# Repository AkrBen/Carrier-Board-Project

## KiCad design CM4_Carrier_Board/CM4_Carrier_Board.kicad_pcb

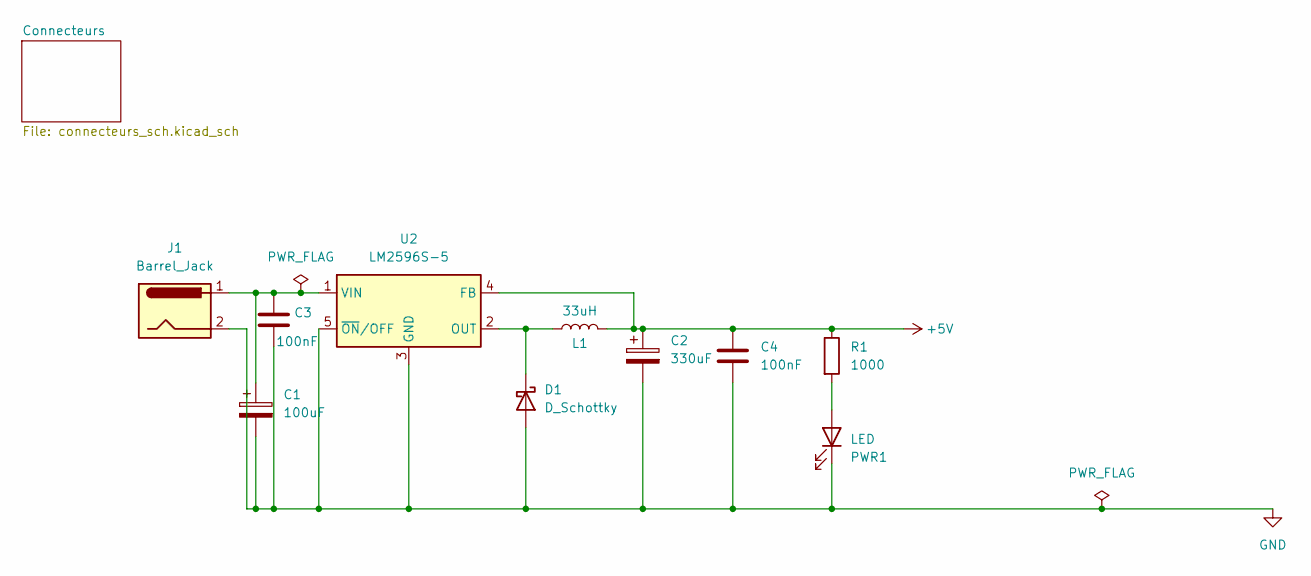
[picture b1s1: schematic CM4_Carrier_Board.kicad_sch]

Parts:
C1: 100uF; CP_Radial_D8.0mm_P3.50mm
C2: 330uF; CP_Radial_D8.0mm_P3.50mm
C3, C4: 100nF; C_Disc_D5.0mm_W2.5mm_P2.50mm
D1: D_Schottky; D_0603_1608Metric
J1: Barrel_Jack; BarrelJack_CUI_PJ-063AH_Horizontal
L1: 33uH; L_0603_1608Metric
PWR1: LED; LED_0603_1608Metric
R1: 1000; R_0603_1608Metric
U2: LM2596S-5; TO-263-5_TabPin3

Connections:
+5V: C2.1, C4.1, L1.2, R1.1, U2.4 (FB); also elsewhere on the board
GND: C1.2, C2.2, C3.2, C4.2, D1.2 (A), J1.2, PWR1.1 (K), U2.3 (GND), U2.5 (~ON/OFF); also elsewhere on the board
unnamed: D1.1 (K), L1.1, U2.2 (OUT)
unnamed: PWR1.2 (A), R1.2
unnamed: C1.1, C3.1, J1.1, U2.1 (VIN)

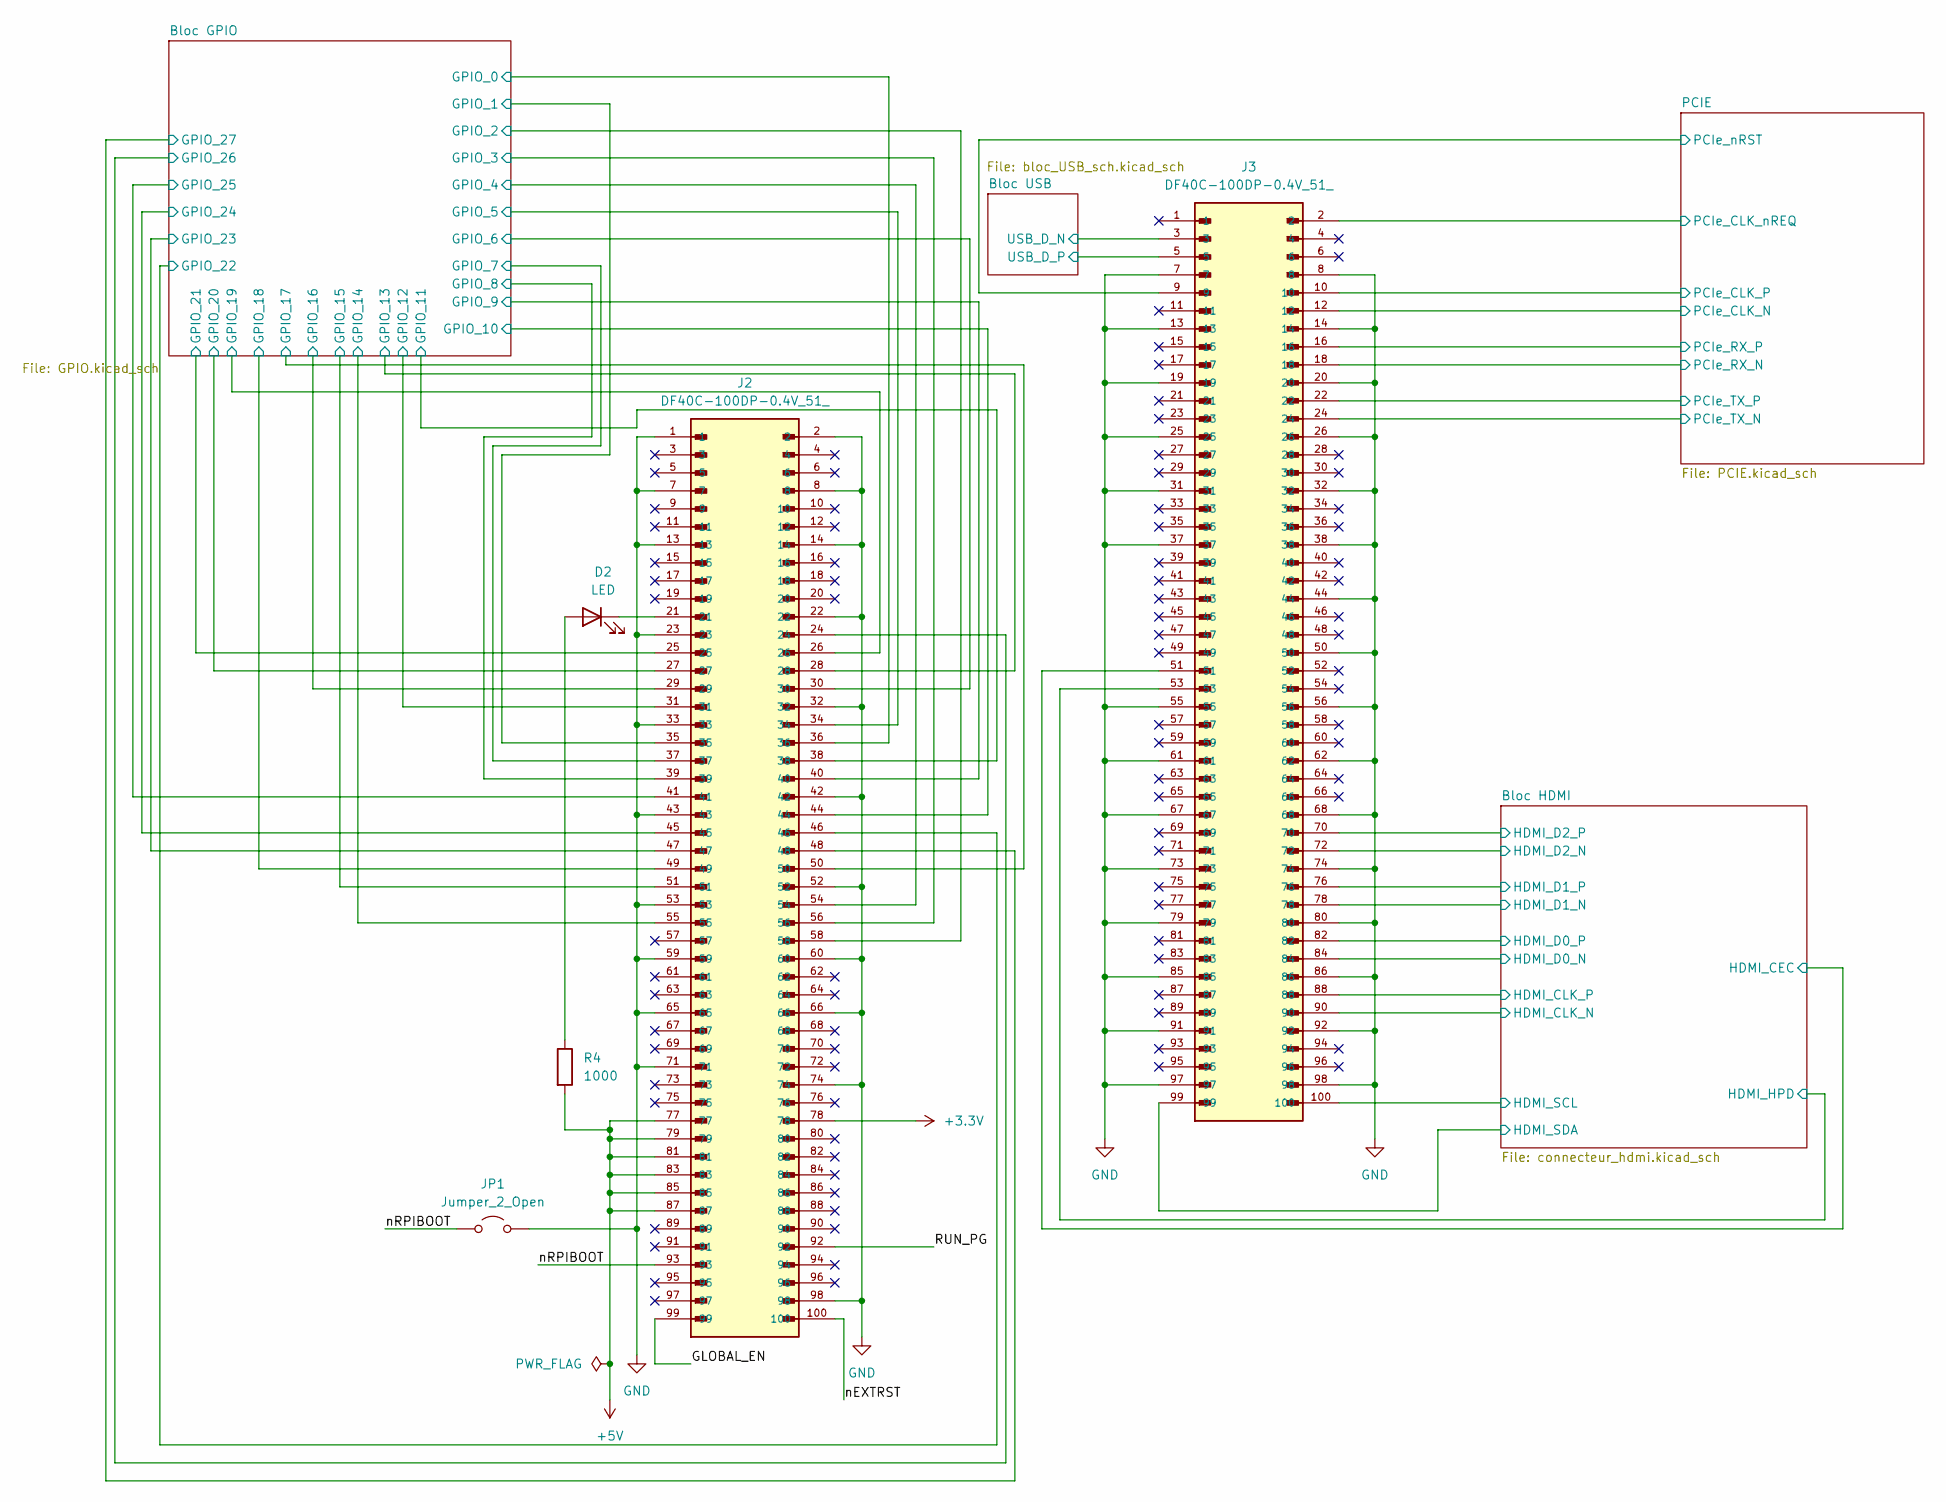
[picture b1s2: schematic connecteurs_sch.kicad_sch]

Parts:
D2: LED; LED_0603_1608Metric
J2, J3: DF40C-100DP-0.4V_51_; HIROSE_DF40C-100DP-0.4V_51_; PARTREV 8
JP1: Jumper_2_Open; PinHeader_1x02_P2.54mm_Vertical
R4: 1000; R_0603_1608Metric

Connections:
+3.3V: J2.78; also elsewhere on the board
+5V: J2.77, J2.79, J2.81, J2.83, J2.85, J2.87, R4.2; also elsewhere on the board
/Connecteurs/Bloc GPIO/GPIO_0: J2.36; also elsewhere on the board
/Connecteurs/Bloc GPIO/GPIO_1: J2.35; also elsewhere on the board
/Connecteurs/Bloc GPIO/GPIO_2: J2.58; also elsewhere on the board
/Connecteurs/Bloc GPIO/GPIO_3: J2.56; also elsewhere on the board
/Connecteurs/Bloc GPIO/GPIO_4: J2.54; also elsewhere on the board
/Connecteurs/Bloc GPIO/GPIO_5: J2.34; also elsewhere on the board
/Connecteurs/Bloc GPIO/GPIO_6: J2.30; also elsewhere on the board
/Connecteurs/Bloc GPIO/GPIO_7: J2.37; also elsewhere on the board
/Connecteurs/Bloc GPIO/GPIO_8: J2.39; also elsewhere on the board
/Connecteurs/Bloc GPIO/GPIO_9: J2.40; also elsewhere on the board
/Connecteurs/Bloc GPIO/GPIO_10: J2.44; also elsewhere on the board
/Connecteurs/Bloc GPIO/GPIO_11: J2.38; also elsewhere on the board
/Connecteurs/Bloc GPIO/GPIO_12: J2.31; also elsewhere on the board
/Connecteurs/Bloc GPIO/GPIO_13: J2.28; also elsewhere on the board
/Connecteurs/Bloc GPIO/GPIO_14: J2.55; also elsewhere on the board
/Connecteurs/Bloc GPIO/GPIO_15: J2.51; also elsewhere on the board
/Connecteurs/Bloc GPIO/GPIO_16: J2.29; also elsewhere on the board
/Connecteurs/Bloc GPIO/GPIO_17: J2.50; also elsewhere on the board
/Connecteurs/Bloc GPIO/GPIO_18: J2.49; also elsewhere on the board
/Connecteurs/Bloc GPIO/GPIO_19: J2.26; also elsewhere on the board
/Connecteurs/Bloc GPIO/GPIO_20: J2.27; also elsewhere on the board
/Connecteurs/Bloc GPIO/GPIO_21: J2.25; also elsewhere on the board
/Connecteurs/Bloc GPIO/GPIO_22: J2.46; also elsewhere on the board
/Connecteurs/Bloc GPIO/GPIO_23: J2.47; also elsewhere on the board
/Connecteurs/Bloc GPIO/GPIO_24: J2.45; also elsewhere on the board
/Connecteurs/Bloc GPIO/GPIO_25: J2.41; also elsewhere on the board
/Connecteurs/Bloc GPIO/GPIO_26: J2.24; also elsewhere on the board
/Connecteurs/Bloc GPIO/GPIO_27: J2.48; also elsewhere on the board
/Connecteurs/Bloc HDMI/HDMI_CEC: J3.51; also elsewhere on the board
/Connecteurs/Bloc HDMI/HDMI_CLK_N: J3.90; also elsewhere on the board
/Connecteurs/Bloc HDMI/HDMI_CLK_P: J3.88; also elsewhere on the board
/Connecteurs/Bloc HDMI/HDMI_D0_N: J3.84; also elsewhere on the board
/Connecteurs/Bloc HDMI/HDMI_D0_P: J3.82; also elsewhere on the board
/Connecteurs/Bloc HDMI/HDMI_D1_N: J3.78; also elsewhere on the board
/Connecteurs/Bloc HDMI/HDMI_D1_P: J3.76; also elsewhere on the board
/Connecteurs/Bloc HDMI/HDMI_D2_N: J3.72; also elsewhere on the board
/Connecteurs/Bloc HDMI/HDMI_D2_P: J3.70; also elsewhere on the board
/Connecteurs/Bloc HDMI/HDMI_HPD: J3.53; also elsewhere on the board
/Connecteurs/Bloc HDMI/HDMI_SCL: J3.100; also elsewhere on the board
/Connecteurs/Bloc HDMI/HDMI_SDA: J3.99; also elsewhere on the board
/Connecteurs/Bloc USB/USB_D_N: J3.3; also elsewhere on the board
/Connecteurs/Bloc USB/USB_D_P: J3.5; also elsewhere on the board
/Connecteurs/GLOBAL_EN: J2.99
/Connecteurs/PCIE/PCIe_CLK_N: J3.12; also elsewhere on the board
/Connecteurs/PCIE/PCIe_CLK_P: J3.10; also elsewhere on the board
/Connecteurs/PCIE/PCIe_CLK_nREQ: J3.2; also elsewhere on the board
/Connecteurs/PCIE/PCIe_RX_N: J3.18; also elsewhere on the board
/Connecteurs/PCIE/PCIe_RX_P: J3.16; also elsewhere on the board
/Connecteurs/PCIE/PCIe_TX_N: J3.24; also elsewhere on the board
/Connecteurs/PCIE/PCIe_TX_P: J3.22; also elsewhere on the board
/Connecteurs/PCIE/PCIe_nRST: J3.9; also elsewhere on the board
/Connecteurs/RUN_PG: J2.92
/Connecteurs/nEXTRST: J2.100
/Connecteurs/nRPIBOOT: J2.93, JP1.1 (A)
GND: J2.1, J2.2, J2.7, J2.8, J2.13, J2.14, J2.22, J2.23, J2.32, J2.33, J2.42, J2.43, J2.52, J2.53, J2.59, J2.60, J2.65, J2.66, J2.71, J2.74, J2.98, J3.7, J3.8, J3.13, J3.14, J3.19, J3.20, J3.25, J3.26, J3.31, J3.32, J3.37, J3.38, J3.44, J3.50, J3.55, J3.56, J3.61, J3.62, J3.67, J3.68, J3.73, J3.74, J3.79, J3.80, J3.85, J3.86, J3.91, J3.92, J3.97, J3.98, JP1.2 (B); also elsewhere on the board
unnamed: D2.2 (A), R4.1
unnamed: D2.1 (K), J2.21

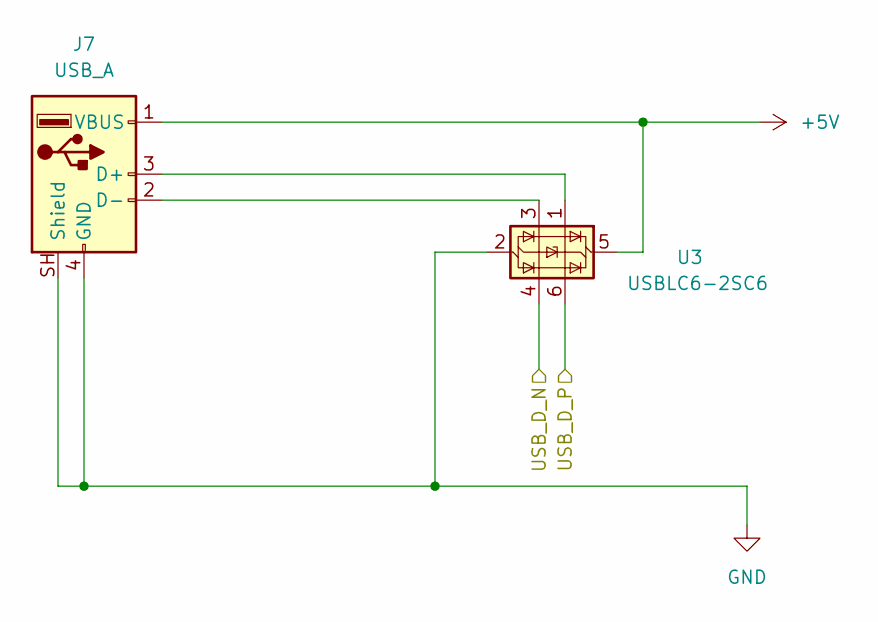
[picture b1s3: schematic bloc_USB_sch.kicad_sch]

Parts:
J7: USB_A; USB_A_Wuerth_614004134726_Horizontal
U3: USBLC6-2SC6; SOT-23-6

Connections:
+5V: J7.1 (VBUS), U3.5 (VBUS); also elsewhere on the board
/Connecteurs/Bloc USB/USB_D_N: U3.4 (I/O2); also elsewhere on the board
/Connecteurs/Bloc USB/USB_D_P: U3.6 (I/O1); also elsewhere on the board
GND: J7.4 (GND), J7.SH (Shield), U3.2 (GND); also elsewhere on the board
unnamed: J7.3 (D+), U3.1 (I/O1)
unnamed: J7.2 (D-), U3.3 (I/O2)

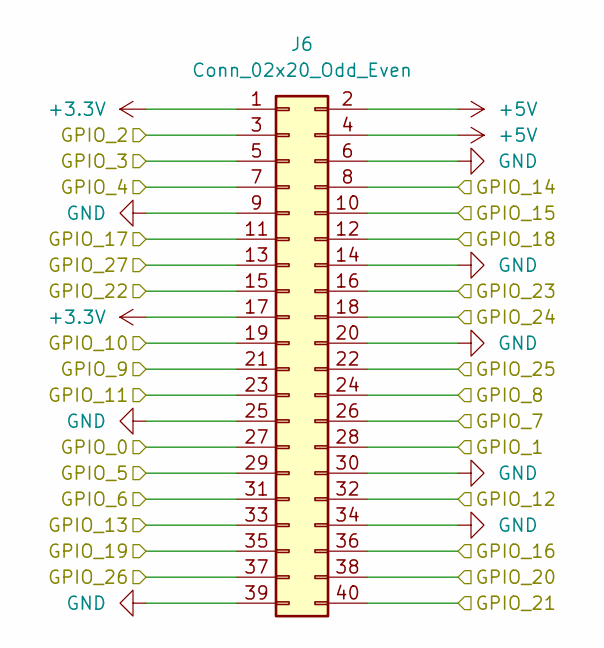
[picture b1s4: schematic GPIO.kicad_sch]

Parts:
J6: Conn_02x20_Odd_Even; PinHeader_2x20_P2.54mm_Vertical

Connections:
+3.3V: J6.1, J6.17; also elsewhere on the board
+5V: J6.2, J6.4; also elsewhere on the board
/Connecteurs/Bloc GPIO/GPIO_0: J6.27; also elsewhere on the board
/Connecteurs/Bloc GPIO/GPIO_1: J6.28; also elsewhere on the board
/Connecteurs/Bloc GPIO/GPIO_2: J6.3; also elsewhere on the board
/Connecteurs/Bloc GPIO/GPIO_3: J6.5; also elsewhere on the board
/Connecteurs/Bloc GPIO/GPIO_4: J6.7; also elsewhere on the board
/Connecteurs/Bloc GPIO/GPIO_5: J6.29; also elsewhere on the board
/Connecteurs/Bloc GPIO/GPIO_6: J6.31; also elsewhere on the board
/Connecteurs/Bloc GPIO/GPIO_7: J6.26; also elsewhere on the board
/Connecteurs/Bloc GPIO/GPIO_8: J6.24; also elsewhere on the board
/Connecteurs/Bloc GPIO/GPIO_9: J6.21; also elsewhere on the board
/Connecteurs/Bloc GPIO/GPIO_10: J6.19; also elsewhere on the board
/Connecteurs/Bloc GPIO/GPIO_11: J6.23; also elsewhere on the board
/Connecteurs/Bloc GPIO/GPIO_12: J6.32; also elsewhere on the board
/Connecteurs/Bloc GPIO/GPIO_13: J6.33; also elsewhere on the board
/Connecteurs/Bloc GPIO/GPIO_14: J6.8; also elsewhere on the board
/Connecteurs/Bloc GPIO/GPIO_15: J6.10; also elsewhere on the board
/Connecteurs/Bloc GPIO/GPIO_16: J6.36; also elsewhere on the board
/Connecteurs/Bloc GPIO/GPIO_17: J6.11; also elsewhere on the board
/Connecteurs/Bloc GPIO/GPIO_18: J6.12; also elsewhere on the board
/Connecteurs/Bloc GPIO/GPIO_19: J6.35; also elsewhere on the board
/Connecteurs/Bloc GPIO/GPIO_20: J6.38; also elsewhere on the board
/Connecteurs/Bloc GPIO/GPIO_21: J6.40; also elsewhere on the board
/Connecteurs/Bloc GPIO/GPIO_22: J6.15; also elsewhere on the board
/Connecteurs/Bloc GPIO/GPIO_23: J6.16; also elsewhere on the board
/Connecteurs/Bloc GPIO/GPIO_24: J6.18; also elsewhere on the board
/Connecteurs/Bloc GPIO/GPIO_25: J6.22; also elsewhere on the board
/Connecteurs/Bloc GPIO/GPIO_26: J6.37; also elsewhere on the board
/Connecteurs/Bloc GPIO/GPIO_27: J6.13; also elsewhere on the board
GND: J6.6, J6.9, J6.14, J6.20, J6.25, J6.30, J6.34, J6.39; also elsewhere on the board

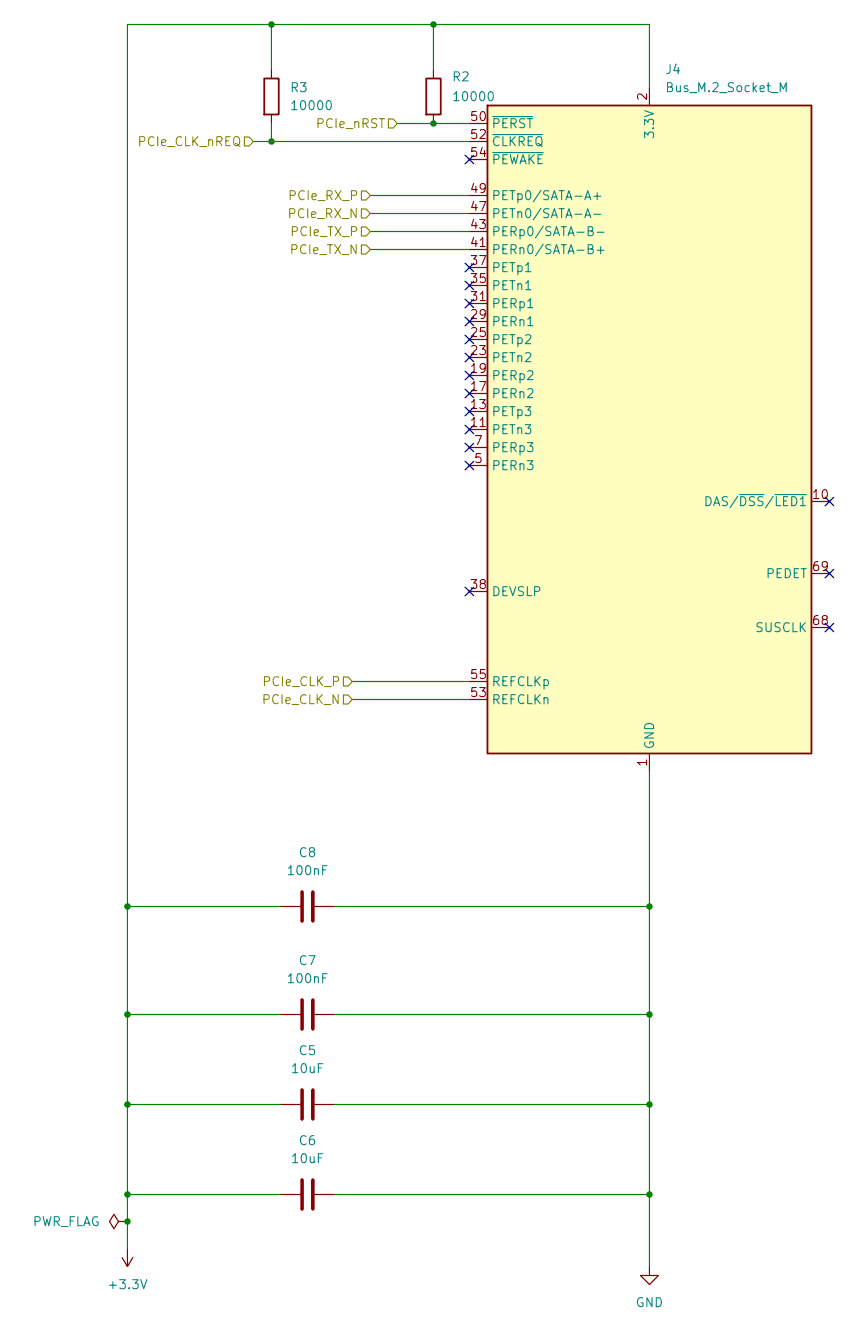
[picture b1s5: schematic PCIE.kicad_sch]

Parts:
C5, C6: 10uF; C_0805_2012Metric
C7, C8: 100nF; C_0603_1608Metric
J4: Bus_M.2_Socket_M; TE_1-2199230-4
R2, R3: 10000; R_0603_1608Metric

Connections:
+3.3V: C5.2, C6.2, C7.2, C8.2, J4.2 (3.3V), J4.4 (3.3V), J4.12 (3.3V), J4.14 (3.3V), J4.16 (3.3V), J4.18 (3.3V), J4.70 (3.3V), J4.72 (3.3V), J4.74 (3.3V), R2.1, R3.1; also elsewhere on the board
/Connecteurs/PCIE/PCIe_CLK_N: J4.53 (REFCLKn); also elsewhere on the board
/Connecteurs/PCIE/PCIe_CLK_P: J4.55 (REFCLKp); also elsewhere on the board
/Connecteurs/PCIE/PCIe_CLK_nREQ: J4.52 (~CLKREQ), R3.2; also elsewhere on the board
/Connecteurs/PCIE/PCIe_RX_N: J4.47 (PETn0/SATA-A-); also elsewhere on the board
/Connecteurs/PCIE/PCIe_RX_P: J4.49 (PETp0/SATA-A+); also elsewhere on the board
/Connecteurs/PCIE/PCIe_TX_N: J4.41 (PERn0/SATA-B+); also elsewhere on the board
/Connecteurs/PCIE/PCIe_TX_P: J4.43 (PERp0/SATA-B-); also elsewhere on the board
/Connecteurs/PCIE/PCIe_nRST: J4.50 (~PERST), R2.2; also elsewhere on the board
GND: C5.1, C6.1, C7.1, C8.1, J4.1 (GND), J4.3 (GND), J4.9 (GND), J4.15 (GND), J4.21 (GND), J4.27 (GND), J4.33 (GND), J4.39 (GND), J4.45 (GND), J4.51 (GND), J4.57 (GND), J4.71 (GND), J4.73 (GND), J4.75 (GND); also elsewhere on the board

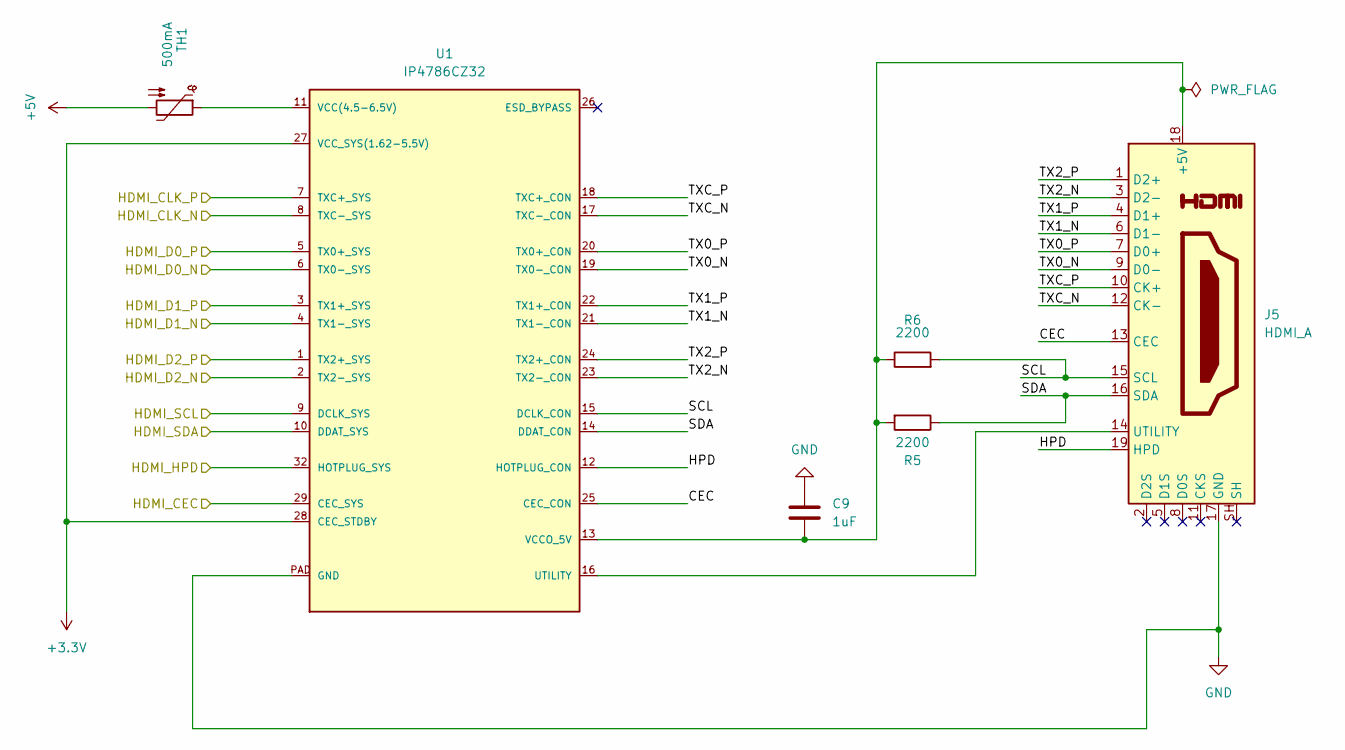
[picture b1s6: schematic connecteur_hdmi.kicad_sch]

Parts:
C9: 1uF; C_0603_1608Metric
J5: HDMI_A; HDMI_A_Amphenol_10029449-x01xLF_Horizontal
R5, R6: 2200; R_0603_1608Metric
TH1: 500mA; Fuse_1206_3216Metric
U1: IP4786CZ32; QFN-32-1EP_5x5mm_P0.5mm_EP3.45x3.45mm

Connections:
+3.3V: U1.27 (VCC_SYS(1.62-5.5V)), U1.28 (CEC_STDBY); also elsewhere on the board
+5V: TH1.2; also elsewhere on the board
/Connecteurs/Bloc HDMI/CEC: J5.13 (CEC), U1.25 (CEC_CON)
/Connecteurs/Bloc HDMI/HDMI_CEC: U1.29 (CEC_SYS); also elsewhere on the board
/Connecteurs/Bloc HDMI/HDMI_CLK_N: U1.8 (TXC-_SYS); also elsewhere on the board
/Connecteurs/Bloc HDMI/HDMI_CLK_P: U1.7 (TXC+_SYS); also elsewhere on the board
/Connecteurs/Bloc HDMI/HDMI_D0_N: U1.6 (TX0-_SYS); also elsewhere on the board
/Connecteurs/Bloc HDMI/HDMI_D0_P: U1.5 (TX0+_SYS); also elsewhere on the board
/Connecteurs/Bloc HDMI/HDMI_D1_N: U1.4 (TX1-_SYS); also elsewhere on the board
/Connecteurs/Bloc HDMI/HDMI_D1_P: U1.3 (TX1+_SYS); also elsewhere on the board
/Connecteurs/Bloc HDMI/HDMI_D2_N: U1.2 (TX2-_SYS); also elsewhere on the board
/Connecteurs/Bloc HDMI/HDMI_D2_P: U1.1 (TX2+_SYS); also elsewhere on the board
/Connecteurs/Bloc HDMI/HDMI_HPD: U1.32 (HOTPLUG_SYS); also elsewhere on the board
/Connecteurs/Bloc HDMI/HDMI_SCL: U1.9 (DCLK_SYS); also elsewhere on the board
/Connecteurs/Bloc HDMI/HDMI_SDA: U1.10 (DDAT_SYS); also elsewhere on the board
/Connecteurs/Bloc HDMI/HPD: J5.19 (HPD), U1.12 (HOTPLUG_CON)
/Connecteurs/Bloc HDMI/SCL: J5.15 (SCL), R6.2, U1.15 (DCLK_CON)
/Connecteurs/Bloc HDMI/SDA: J5.16 (SDA), R5.1, U1.14 (DDAT_CON)
/Connecteurs/Bloc HDMI/TX0_N: J5.9 (D0-), U1.19 (TX0-_CON)
/Connecteurs/Bloc HDMI/TX0_P: J5.7 (D0+), U1.20 (TX0+_CON)
/Connecteurs/Bloc HDMI/TX1_N: J5.6 (D1-), U1.21 (TX1-_CON)
/Connecteurs/Bloc HDMI/TX1_P: J5.4 (D1+), U1.22 (TX1+_CON)
/Connecteurs/Bloc HDMI/TX2_N: J5.3 (D2-), U1.23 (TX2-_CON)
/Connecteurs/Bloc HDMI/TX2_P: J5.1 (D2+), U1.24 (TX2+_CON)
/Connecteurs/Bloc HDMI/TXC_N: J5.12 (CK-), U1.17 (TXC-_CON)
/Connecteurs/Bloc HDMI/TXC_P: J5.10 (CK+), U1.18 (TXC+_CON)
GND: C9.1, J5.17 (GND), U1.PAD (GND); also elsewhere on the board
unnamed: C9.2, J5.18 (+5V), R5.2, R6.1, U1.13 (VCCO_5V)
unnamed: J5.14 (UTILITY), U1.16 (UTILITY)
unnamed: TH1.1, U1.11 (VCC(4.5-6.5V))

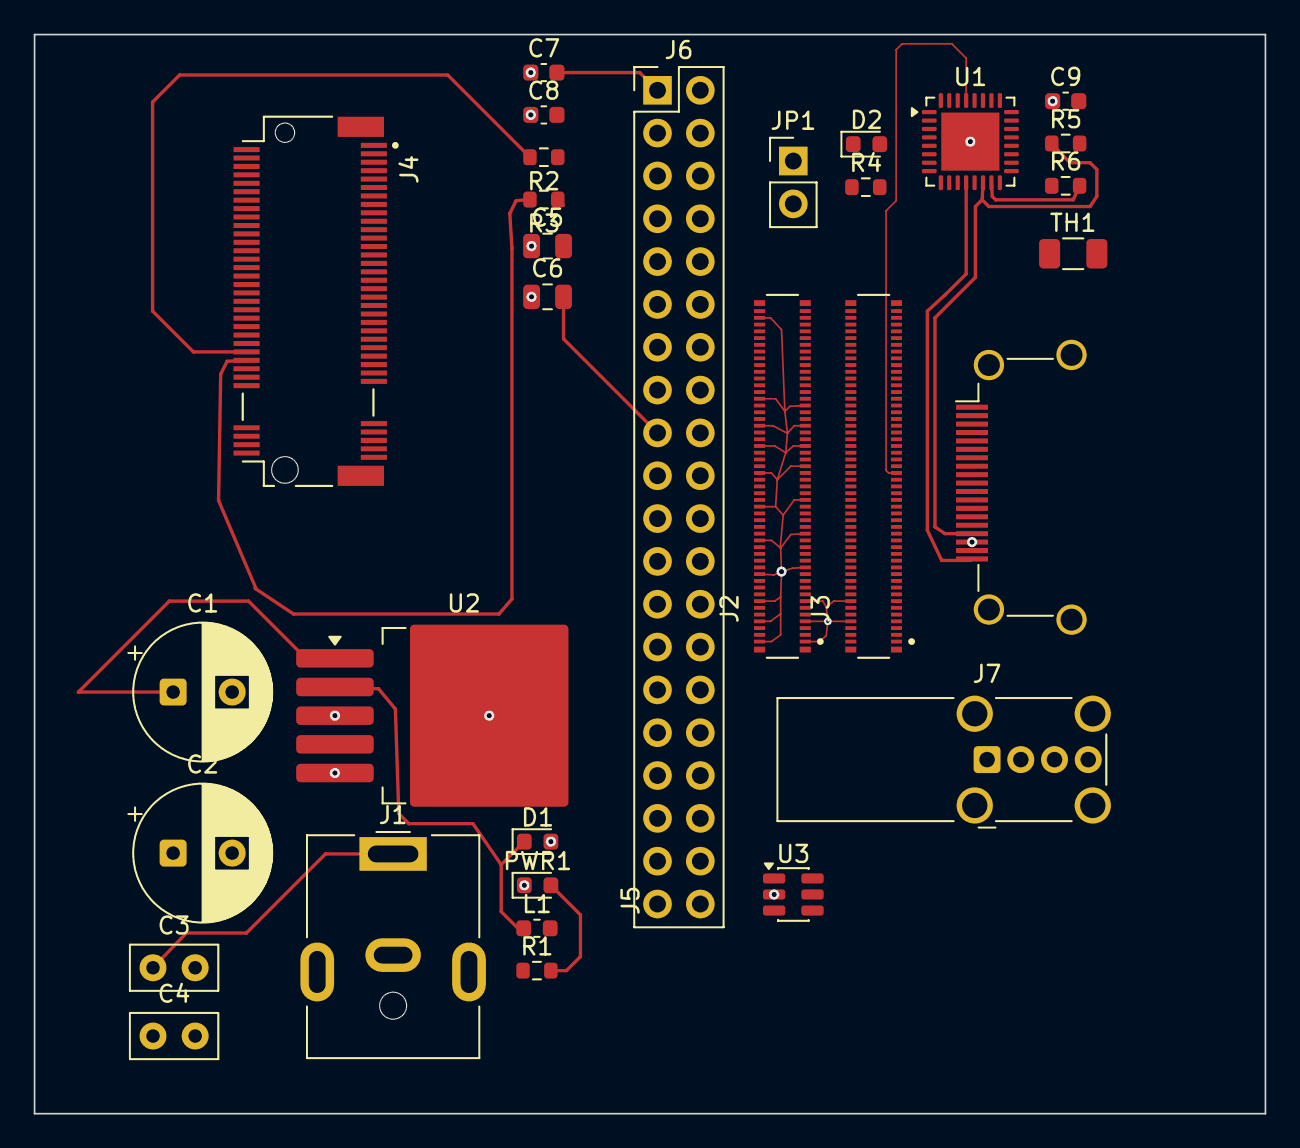
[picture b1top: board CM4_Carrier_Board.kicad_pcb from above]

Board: 4 copper layers, 73.0 x 64.0 mm, 31 parts (0 on the bottom side), 76 nets.
